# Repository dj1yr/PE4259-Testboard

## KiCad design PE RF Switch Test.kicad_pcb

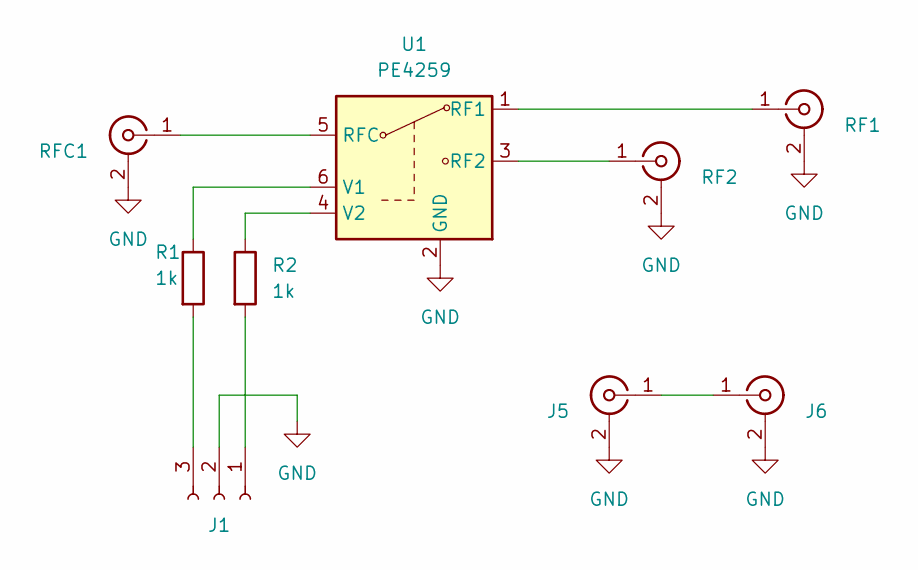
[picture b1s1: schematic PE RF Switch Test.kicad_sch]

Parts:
J1: Conn_01x03_Socket; JST_EH_B3B-EH-A_1x03_P2.50mm_Vertical
J5, J6: Conn_Coaxial; SMA_Molex_73251-1153_EdgeMount_Horizontal
R1, R2: 1k; R_0603_1608Metric_Pad0.98x0.95mm_HandSolder
RF1, RF2: Conn_Coaxial; SMA_Molex_73251-1153_EdgeMount_Horizontal
RFC1: Conn_Coaxial; SMA_Molex_73251-1153_EdgeMount_Horizontal
U1: PE4259; SOT-363_SC-70-6_Handsoldering

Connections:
GND: J1.2, J5.2 (Ext), J6.2 (Ext), RF1.2 (Ext), RF2.2 (Ext), RFC1.2 (Ext), U1.2 (GND)
unnamed: J1.1, R2.2
unnamed: J1.3, R1.2
unnamed: J5.1 (In), J6.1 (In)
unnamed: RF1.1 (In), U1.1 (RF1)
unnamed: RF2.1 (In), U1.3 (RF2)
unnamed: RFC1.1 (In), U1.5 (RFC)
unnamed: R1.1, U1.6 (V1)
unnamed: R2.1, U1.4 (V2)

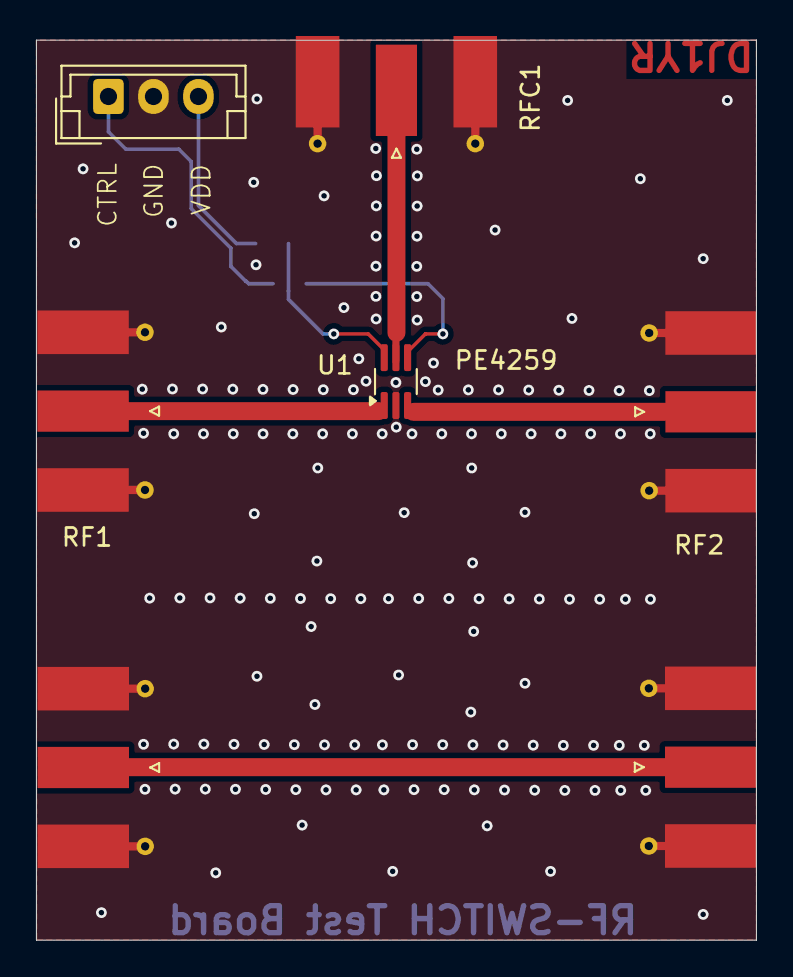
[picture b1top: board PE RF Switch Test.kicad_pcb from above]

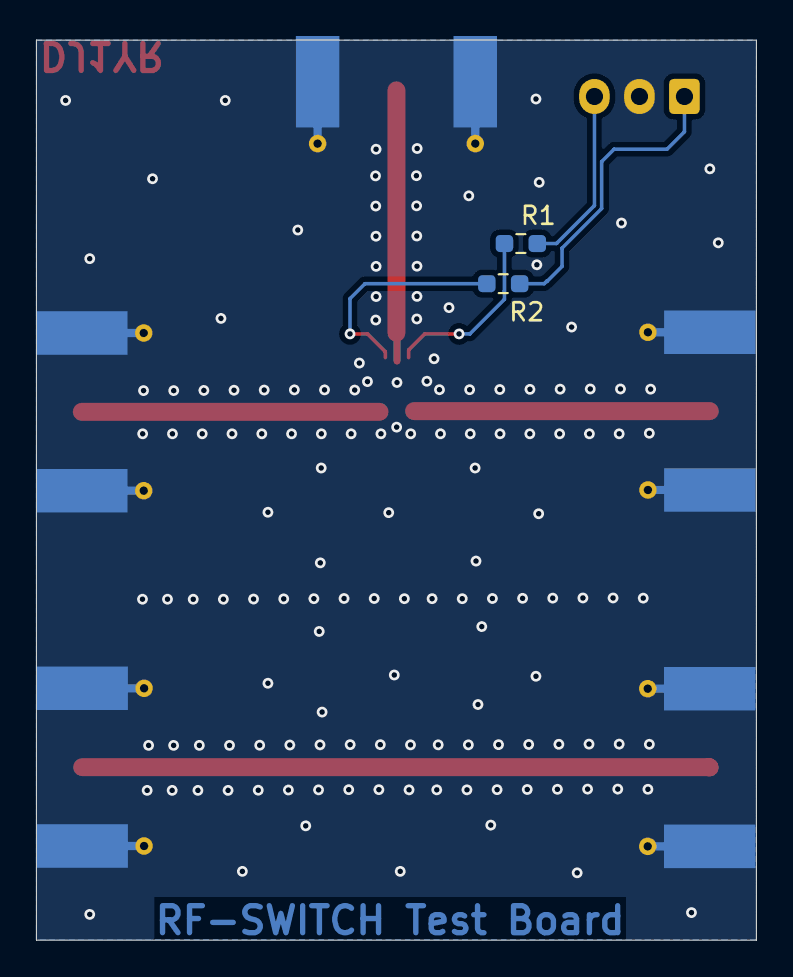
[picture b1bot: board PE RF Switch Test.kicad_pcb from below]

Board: 2 copper layers, 40.0 x 50.0 mm, 9 parts (2 on the bottom side), 9 nets.
